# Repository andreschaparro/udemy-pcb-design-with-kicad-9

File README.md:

# udemy | PCB design with KiCad - updated for KiCad 9

Dr. Peter Dalmaris

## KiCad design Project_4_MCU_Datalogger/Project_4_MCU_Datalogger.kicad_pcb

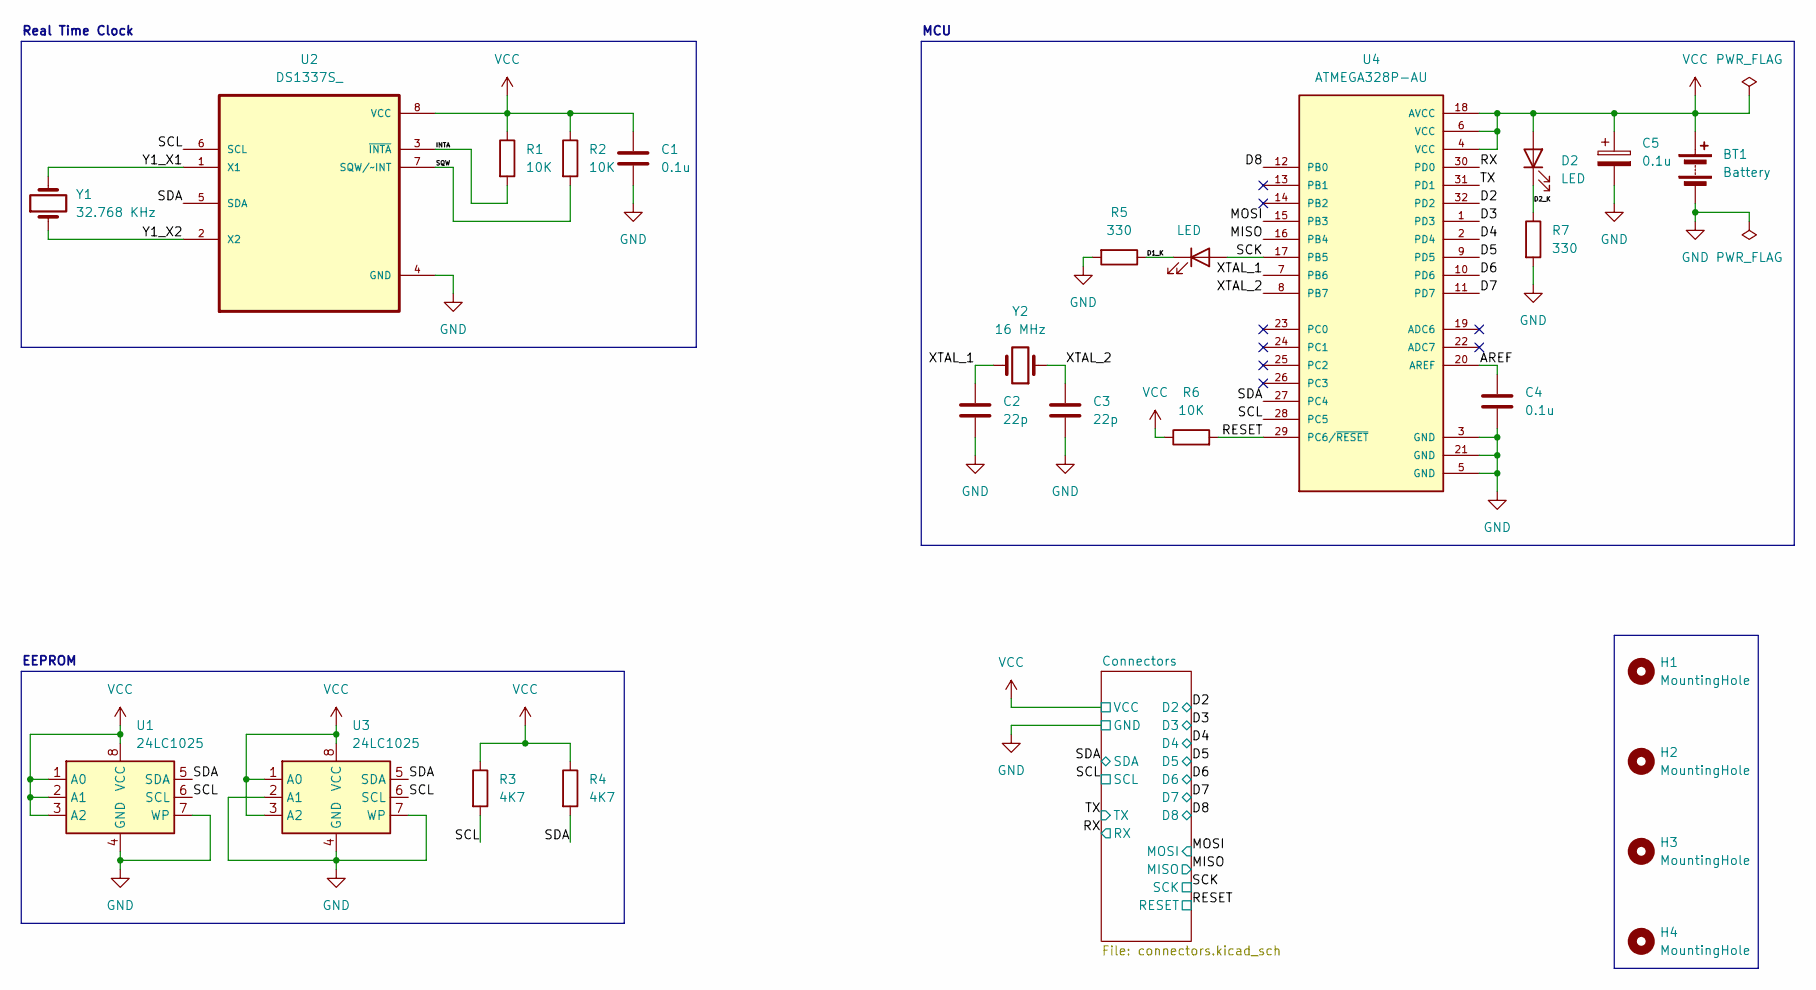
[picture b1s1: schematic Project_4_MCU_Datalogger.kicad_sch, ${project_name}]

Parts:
BT1: Battery; PinHeader_1x02_P2.54mm_Vertical
C1, C4, C5: 0.1u; C_0805_2012Metric
C2, C3: 22p; C_0805_2012Metric
D1, D2: LED; LED_0805_2012Metric
H1, H2, H3, H4: MountingHole; MountingHole_2.1mm
R1, R2, R6: 10K; R_0805_2012Metric
R3, R4: 4K7; R_0805_2012Metric
R5, R7: 330; R_0805_2012Metric
U1, U3: 24LC1025; SOIC-8_5.3x5.3mm_P1.27mm
U2: DS1337S_; SOIC127P600X175-8N
U4: ATMEGA328P-AU; QFP80P900X900X120-32N; PARTREV 8271A
Y1: 32.768 KHz; Crystal_SMD_5032-2Pin_5.0x3.2mm_HandSoldering
Y2: 16 MHz; Crystal_SMD_5032-2Pin_5.0x3.2mm_HandSoldering

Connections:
/AREF: C4.1, U4.20 (AREF)
/D1_K: D1.1 (K), R5.1
/D2: U4.32 (PD2); also elsewhere on the board
/D2_K: D2.1 (K), R7.1
/D3: U4.1 (PD3); also elsewhere on the board
/D4: U4.2 (PD4); also elsewhere on the board
/D5: U4.9 (PD5); also elsewhere on the board
/D6: U4.10 (PD6); also elsewhere on the board
/D7: U4.11 (PD7); also elsewhere on the board
/D8: U4.12 (PB0); also elsewhere on the board
/INTA: R1.2, U2.3 (~INTA)
/MISO: U4.16 (PB4); also elsewhere on the board
/MOSI: U4.15 (PB3); also elsewhere on the board
/RESET: R6.2, U4.29 (PC6/~RESET); also elsewhere on the board
/RX: U4.30 (PD0); also elsewhere on the board
/SCK: D1.2 (A), U4.17 (PB5); also elsewhere on the board
/SCL: R3.2, U1.6 (SCL), U2.6 (SCL), U3.6 (SCL), U4.28 (PC5); also elsewhere on the board
/SDA: R4.2, U1.5 (SDA), U2.5 (SDA), U3.5 (SDA), U4.27 (PC4); also elsewhere on the board
/SQW: R2.2, U2.7 (SQW/~INT)
/TX: U4.31 (PD1); also elsewhere on the board
/XTAL_1: C2.1, U4.7 (PB6), Y2.2
/XTAL_2: C3.1, U4.8 (PB7), Y2.1
/Y1_X1: U2.1 (X1), Y1.2
/Y1_X2: U2.2 (X2), Y1.1
GND: BT1.2 (-), C1.2, C2.2, C3.2, C4.2, C5.2, R5.2, R7.2, U1.4 (GND), U1.7 (WP), U2.4 (GND), U3.2 (A1), U3.4 (GND), U3.7 (WP), U4.3 (GND), U4.5 (GND), U4.21 (GND); also elsewhere on the board
VCC: BT1.1 (+), C1.1, C5.1, D2.2 (A), R1.1, R2.1, R3.1, R4.1, R6.1, U1.1 (A0), U1.2 (A1), U1.3 (A2), U1.8 (VCC), U2.8 (VCC), U3.1 (A0), U3.3 (A2), U3.8 (VCC), U4.4 (VCC), U4.6 (VCC), U4.18 (AVCC); also elsewhere on the board

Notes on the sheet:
Real Time Clock
EEPROM
MCU

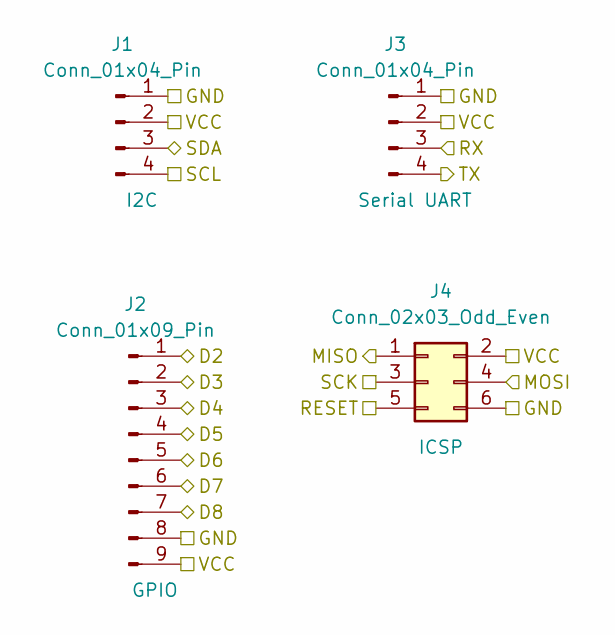
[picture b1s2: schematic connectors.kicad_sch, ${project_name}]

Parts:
J1, J3: Conn_01x04_Pin; PinHeader_1x04_P2.54mm_Vertical
J2: Conn_01x09_Pin; PinHeader_1x09_P2.54mm_Vertical
J4: Conn_02x03_Odd_Even; PinHeader_2x03_P2.54mm_Vertical

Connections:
/D2: J2.1; also elsewhere on the board
/D3: J2.2; also elsewhere on the board
/D4: J2.3; also elsewhere on the board
/D5: J2.4; also elsewhere on the board
/D6: J2.5; also elsewhere on the board
/D7: J2.6; also elsewhere on the board
/D8: J2.7; also elsewhere on the board
/MISO: J4.1; also elsewhere on the board
/MOSI: J4.4; also elsewhere on the board
/RESET: J4.5; also elsewhere on the board
/RX: J3.3; also elsewhere on the board
/SCK: J4.3; also elsewhere on the board
/SCL: J1.4; also elsewhere on the board
/SDA: J1.3; also elsewhere on the board
/TX: J3.4; also elsewhere on the board
GND: J1.1, J2.8, J3.1, J4.6; also elsewhere on the board
VCC: J1.2, J2.9, J3.2, J4.2; also elsewhere on the board

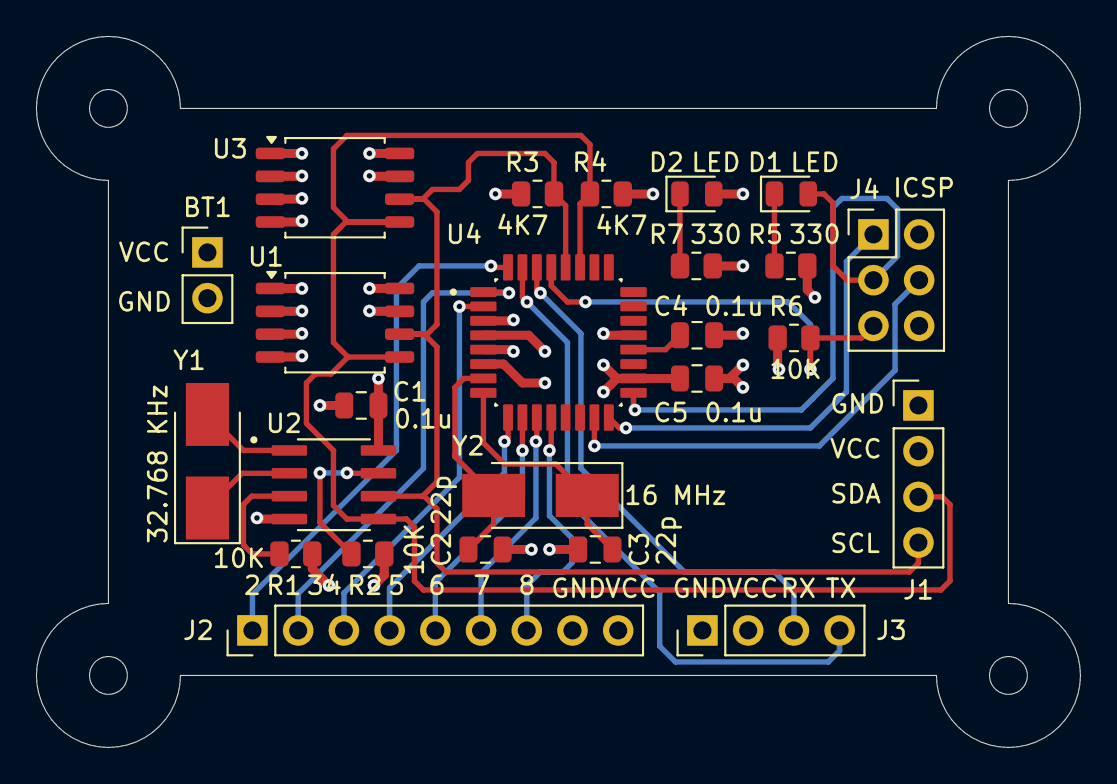
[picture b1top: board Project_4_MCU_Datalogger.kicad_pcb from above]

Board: 4 copper layers, 58.0 x 39.5 mm, 29 parts (0 on the bottom side), 26 nets.

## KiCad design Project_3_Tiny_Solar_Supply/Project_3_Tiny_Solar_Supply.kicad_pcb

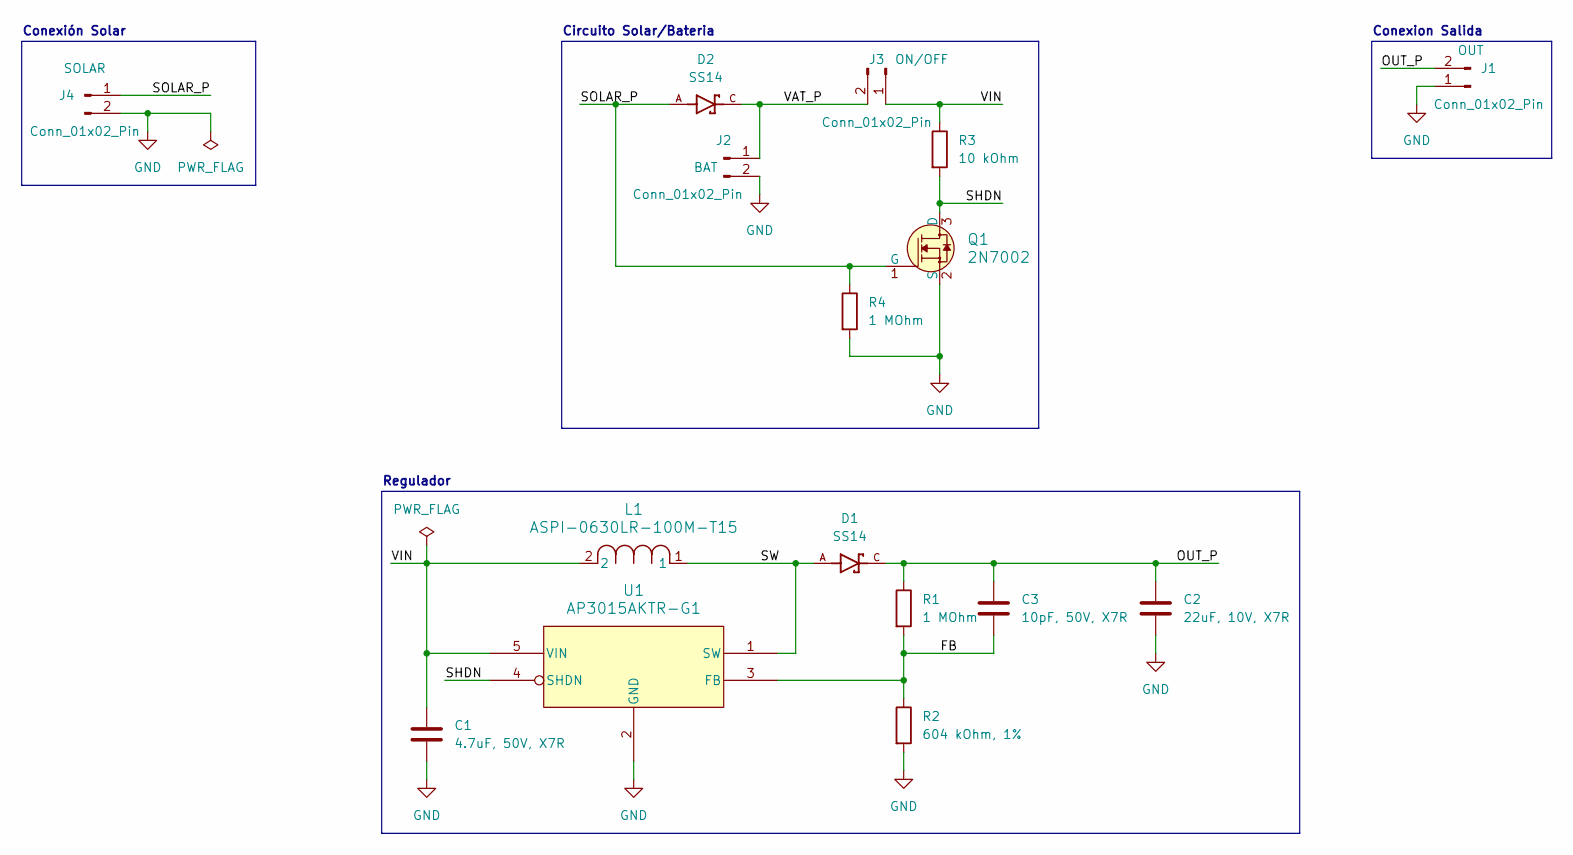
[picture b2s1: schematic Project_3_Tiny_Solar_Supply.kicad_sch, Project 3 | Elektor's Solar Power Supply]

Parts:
C1: 4.7uF, 50V, X7R; C_0805_2012Metric
C2: 22uF, 10V, X7R; C_1206_3216Metric
C3: 10pF, 50V, X7R; C_0805_2012Metric
D1, D2: SS14; DIOM4325X250N; PARTREV O2102
J1, J2, J4: Conn_01x02_Pin; PinHeader_1x02_P2.54mm_Horizontal
J3: Conn_01x02_Pin; SW_DIP_SPSTx01_Slide_9.78x4.72mm_W7.62mm_P2.54mm
L1: ASPI-0630LR-100M-T15; IND_ASPI-0630LR_ABR
Q1: 2N7002; SOT-23-3; MPN 2N7002; Digi-Key_PN 2N7002NCT-ND
R1, R4: 1 MOhm; R_0805_2012Metric
R2: 604 kOhm, 1%; R_0805_2012Metric
R3: 10 kOhm; R_0805_2012Metric
U1: AP3015AKTR-G1; SOT23-5_1P55X2P9_DIO

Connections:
/FB: C3.2, R1.2, R2.1, U1.3 (FB)
/OUT_P: C2.1, C3.1, D1.C, J1.2, R1.1
/SHDN: Q1.3 (D), R3.2, U1.4 (SHDN)
/SOLAR_P: D2.A, J4.1, Q1.1 (G), R4.1
/SW: D1.A, L1.1, U1.1 (SW)
/VAT_P: D2.C, J2.1, J3.2
/VIN: C1.1, J3.1, L1.2, R3.1, U1.5 (VIN)
GND: C1.2, C2.2, J1.1, J2.2, J4.2, Q1.2 (S), R2.2, R4.2, U1.2 (GND)

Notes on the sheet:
Conexion Salida
Circuito Solar/Bateria
Conexión Solar
Regulador

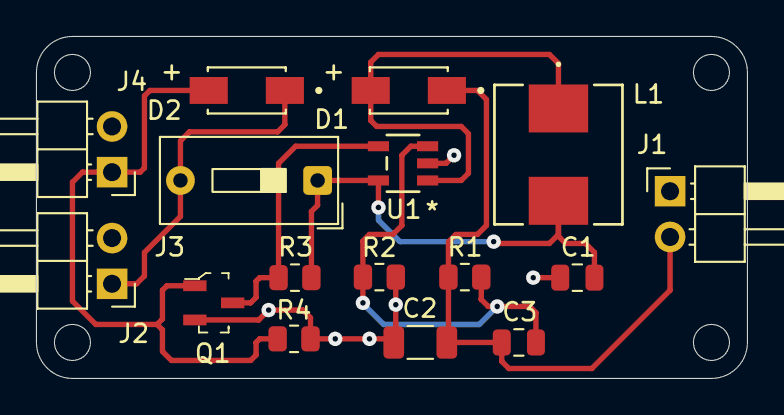
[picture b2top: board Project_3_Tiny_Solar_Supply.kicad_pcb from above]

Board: 2 copper layers, 39.5 x 19.0 mm, 16 parts (0 on the bottom side), 8 nets.

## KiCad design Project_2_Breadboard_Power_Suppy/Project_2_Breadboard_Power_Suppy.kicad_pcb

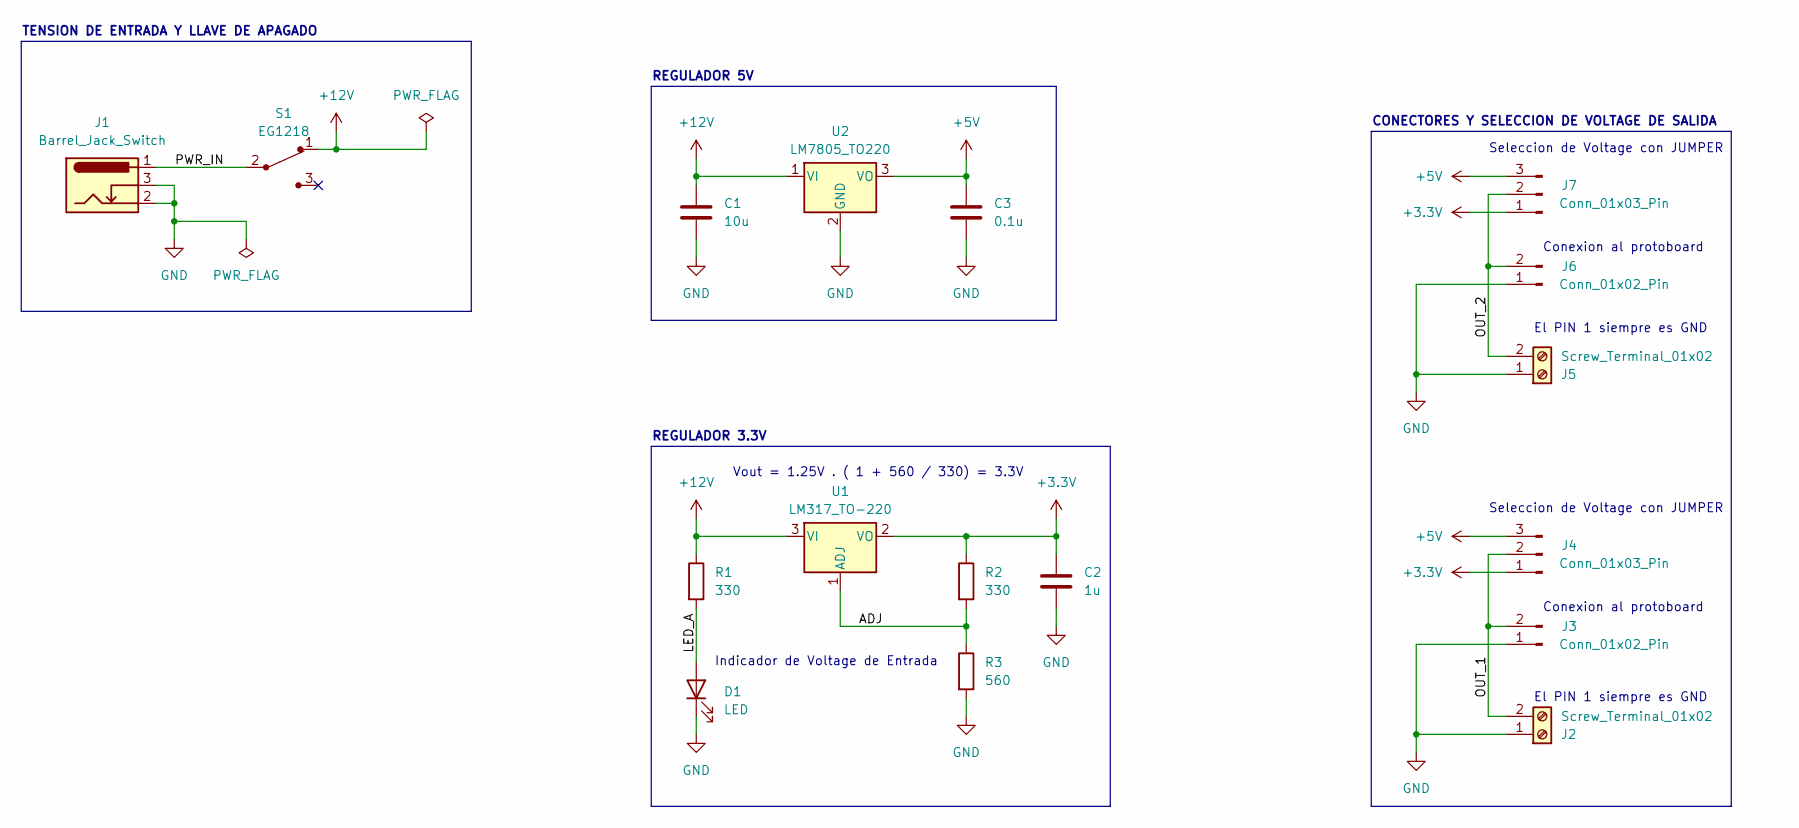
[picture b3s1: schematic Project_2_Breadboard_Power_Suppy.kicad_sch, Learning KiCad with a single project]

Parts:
C1: 10u; C_Disc_D3.0mm_W1.6mm_P2.50mm
C2: 1u; C_Disc_D3.0mm_W1.6mm_P2.50mm
C3: 0.1u; C_Disc_D3.0mm_W1.6mm_P2.50mm
D1: LED; LED_D5.0mm
J1: Barrel_Jack_Switch; BarrelJack_Horizontal
J2, J5: Screw_Terminal_01x02; TerminalBlock_bornier-2_P5.08mm
J3, J6: Conn_01x02_Pin; PinHeader_1x02_P2.54mm_Vertical
J4, J7: Conn_01x03_Pin; PinHeader_1x03_P2.54mm_Vertical
R1, R2: 330; R_Axial_DIN0204_L3.6mm_D1.6mm_P7.62mm_Horizontal
R3: 560; R_Axial_DIN0204_L3.6mm_D1.6mm_P7.62mm_Horizontal
S1: EG1218; Switch_Slide_11.6x4mm_EG1218; MPN EG1218; Digi-Key_PN EG1903-ND
U1: LM317_TO-220; TO-220-3_Vertical
U2: LM7805_TO220; TO-220-3_Vertical

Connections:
+3.3V: C2.1, J4.1, J7.1, R2.1, U1.2 (VO)
+5V: C3.1, J4.3, J7.3, U2.3 (VO)
+12V: C1.1, R1.1, S1.1, U1.3 (VI), U2.1 (VI)
/ADJ: R2.2, R3.1, U1.1 (ADJ)
/LED_A: D1.2 (A), R1.2
/OUT_1: J2.2, J3.2, J4.2
/OUT_2: J5.2, J6.2, J7.2
/PWR_IN: J1.1, S1.2
GND: C1.2, C2.2, C3.2, D1.1 (K), J1.2, J1.3, J2.1, J3.1, J5.1, J6.1, R3.2, U2.2 (GND)

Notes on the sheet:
REGULADOR 5V
TENSION DE ENTRADA Y LLAVE DE APAGADO
El PIN 1 siempre es GND
Conexion al protoboard
Seleccion de Voltage con JUMPER
Indicador de Voltage de Entrada
CONECTORES Y SELECCION DE VOLTAGE DE SALIDA
Vout = 1.25V . ( 1 + 560 / 330) = 3.3V
REGULADOR 3.3V

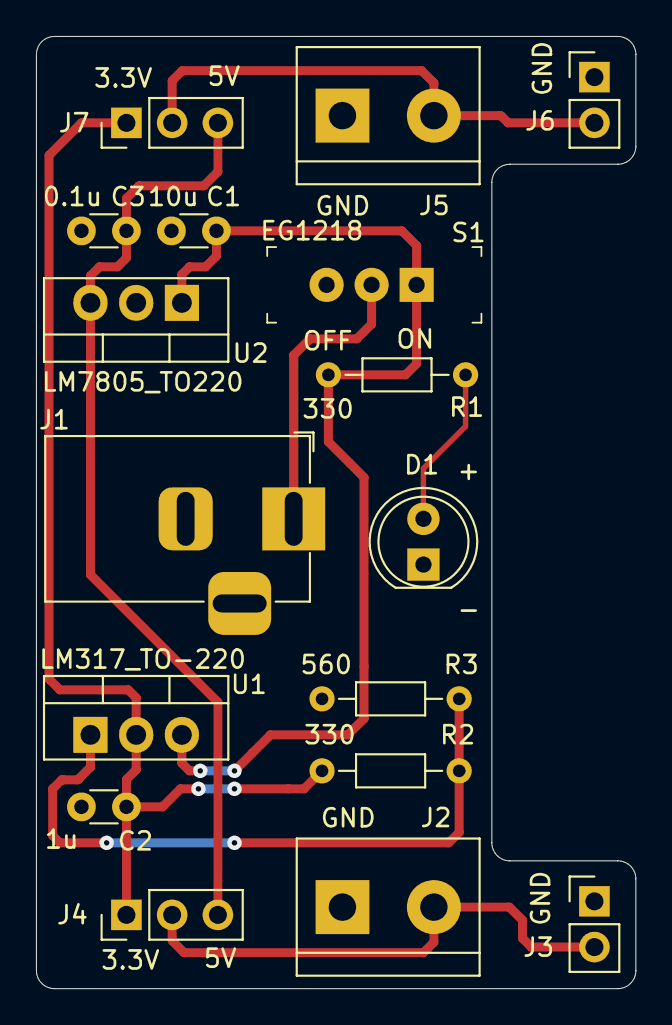
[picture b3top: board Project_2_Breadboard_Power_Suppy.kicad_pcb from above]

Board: 2 copper layers, 33.3 x 52.9 mm, 17 parts (0 on the bottom side), 9 nets.

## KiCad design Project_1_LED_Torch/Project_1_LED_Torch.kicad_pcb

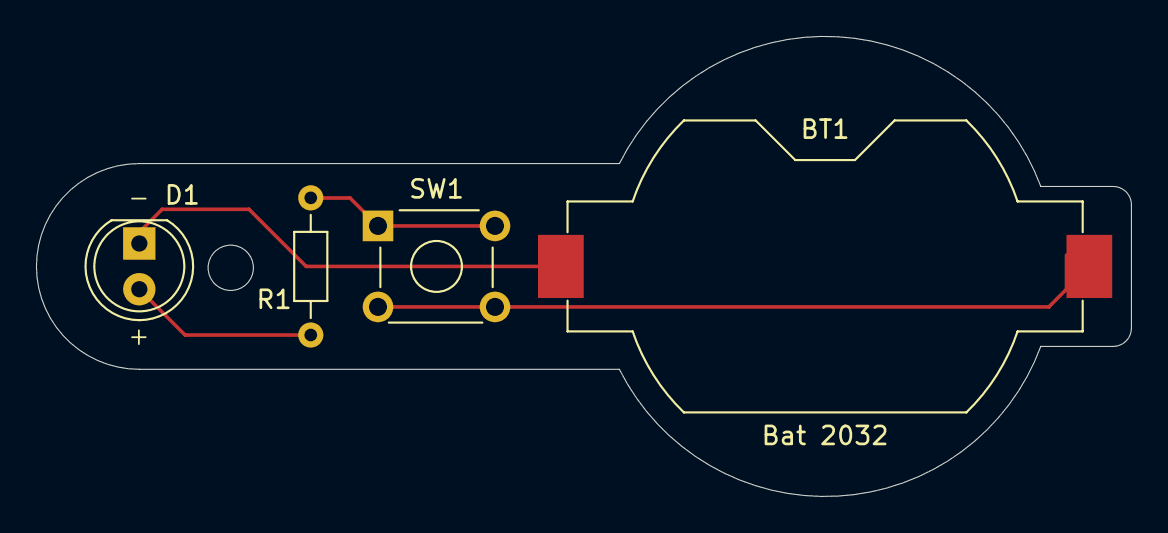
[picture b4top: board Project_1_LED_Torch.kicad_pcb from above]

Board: 2 copper layers, 60.8 x 25.6 mm, 4 parts (0 on the bottom side), 4 nets.

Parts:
BT1: Bat 2032; BatteryHolder_Keystone_1058_1x2032
D1: LED; LED_D5.0mm
R1: R; R_Axial_DIN0204_L3.6mm_D1.6mm_P7.62mm_Horizontal
SW1: SW_DPST_x2; SW_TH_Tactile_Omron_B3F-10xx

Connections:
/LED_anode: D1.2 (A), R1.1
/LED_cathode: BT1.2 (-), D1.1 (K)
/bat_pos: BT1.1 (+), SW1.2 (B)
unnamed: R1.2, SW1.1 (A)

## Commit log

2025-05-19 project 2 complete
2025-05-20 project 3 complete
2025-05-21 project 4 started
2025-05-21 eeschema setup complete
2025-05-21 project 4 symbols added
2025-05-21 project 4 symbols arranged
2025-05-21 project 4 added components values
2025-05-21 project 4 completed symbol-footprint associations
2025-05-21 completed wiring
2025-05-21 schematic completed
2025-05-21 setup pcbnew
2025-05-22 completed placement of footprints
2025-05-23 pcb completed
2025-05-23 fabrication files jlcpcb
2025-05-23 pcb 4layer completed
2025-05-26 added .gitattributes file to ignore PCB files during merge
2025-05-26 completed
